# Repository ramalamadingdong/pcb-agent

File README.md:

# pcb-agent

Design a circuit board end to end with an agent. Parts, netlist, placement,
routing, gerbers a fab will build. You review, it does the work.

<p align="center"><em>The example board —
<a href="examples/unoq-power-shield">examples/unoq-power-shield</a>, 49 components
on four layers, routed to 0 unconnected and 0 clearance violations. A KiCad render
of the design files in this repo; <strong>no physical board has been
fabricated</strong>.</em></p>

The method: **the design lives in a CSV, not in KiCad.** One row per pin.
Scripts build the schematic and the board from it. Nothing in the KiCad files
is edited by hand — to change the circuit you edit a row and rebuild. Then
five levels of checking, the last of which parses the exported gerbers,
because the gerbers are what the factory builds.

Written up in full at
[mouro.ai/blog/pcb-design-with-ai](https://mouro.ai/blog/pcb-design-with-ai/)
— why the CSV is the source of truth, the tool behaviour each pass exists
to survive, and what the example board cost to finish.

**New here? [docs/end-to-end.md](docs/end-to-end.md)** is the whole path in
one page: install, prove the toolchain on the example, then your own board
from an idea to a fab package.

## Status: passes landed, example board unproven

The build passes are in `scripts/build/` and the whole pipeline runs end to
end against the example board: netlist → schematic (clean round-trip diff) →
board → netclasses → floorplan → holes → zones/fanout → freerouting →
completion → fab export → checker. As of 2026-08-30 the example has passed
its pre-order gates — **0 unconnected, 0 clearance violations** across 5
identical DRC runs, `validate_gerbers` 14/0, `check_placement` 5/0, ERC
clean, every residual DRC item explained in its `rev-1-plan.md` ledger — but
**no physical board has been fabricated yet**. Until one comes back and powers on, treat
`examples/unoq-power-shield` as a pipeline exercise, not a verified
reference design.

**2026-09-30: three defects found and fixed, example rebuilt.** New gates
caught three real defects that the earlier gates had passed:

- **J4 (Qwiic) was rotated 180°.** Its socket opened into the board.
  `check_placement` now derives which way a connector faces from its
  rotation. J4 is at 0° now.
- **16 pads on eight rotated passives lay along the part axis.**
  `fix_pad_angles --check` now gates on it.
- **`finish_routes` laid redundant copper on already-routed nets.** Its
  connectivity model never joined a segment's two ends. That is fixed, and
  roughly 200 redundant segments and 69 vias are gone.

The example was rebuilt from `netlist.csv` in the pinned container.
`make check` passes every gate:

- ERC: 0 errors.
- Pad angles: all correct.
- DRC ×5: 13 errors, all in the `[[drc.accept]]` ledger with reasons, 0
  unconnected, identical in every run.
- `check_placement`: 11/0.
- `validate_gerbers`: 15/0, including the IPC-D-356 netlist against
  `netlist.csv`, 159/159 pins.

It is still **unfabricated**. See `rev-1-plan.md` for what remains at order
time.

If you want only the fab-output checker, it stands alone with no dependencies
at [gerber-check](https://github.com/ramalamadingdong/gerber-check).

Platform honesty: developed and verified on Linux (WSL) — the container
path, the clean-box doctor advice, and the whole pipeline. **macOS is
untested**: `doctor.py`'s KiCad.app python path was written from
documentation, not a Mac, and is the most likely thing to be wrong. If you
hit it, an issue with your `doctor.py` output is gold.

## Setup

```bash
git clone https://github.com/ramalamadingdong/pcb-agent && cd pcb-agent
python3 scripts/doctor.py
```

The doctor names every missing piece and the fix for your OS. Five things have
to line up — KiCad (9 or 10, **matching the major your boards use**: a KiCad 9
pcbnew returns None loading a KiCad 10 board, no error), KiCad's bundled
Python, a JVM matching your Freerouting, the Freerouting jar, and `uv` — and
each fails in a way that wastes an afternoon if you don't know what you're
looking at.

### Or: the container

The headless stages run in a container instead, so KiCad, Java and
Freerouting never need installing by hand:

```bash
make setup     # builds the pcb-agent image; fetches the pinned Freerouting
               # jar to tools/ for native runs, checksum-verified
make doctor    # reports what the container satisfies
make build route export check   # run in-container automatically when the
                                # image exists (BOARD_DIR picks the board)
```

`./run.sh <cmd>` runs any command in the container with the repo mounted at
/work, as your uid/gid. You still install KiCad natively to *look* at the
board — the container has no GUI (the one X11 artifact inside is xvfb, a
virtual framebuffer that exists solely because Freerouting 1.9.0 asks for a
screen size it never uses). The base image is digest-pinned (`KICAD_BASE` in
the Makefile) and must match your native KiCad major; the doctor warns on
drift. kicad/kicad images are linux/amd64 — Apple Silicon runs them under
emulation.

Then, in Claude Code:

```
/plugin marketplace add aklofas/kicad-happy
/plugin install kicad-happy@kicad-happy
```

Eleven KiCad skills by Andrew Klofas — datasheet extraction, EMC, SPICE,
sourcing from DigiKey, Mouser, LCSC and element14, fab prep for JLCPCB and
PCBWay. MIT. This is the install that matters most.

## Use

```
/new-board     an idea, interviewed into a cited plan and a netlist.csv
/build         netlist.csv -> schematic -> board -> placement -> zones -> silk
/route         snapshot -> Freerouting -> DRC x5 -> gerbers
/check         ERC, pad angles, DRC x5, placement, and the fab package, all gated
/improve-placement   look at where routing got stuck, try floorplan edits,
               keep only what a rebuild + re-route measures as better
/doctor        is this machine able to run any of it
```

`/new-board` stops twice for your sign-off: once after the interview, once
before it writes the netlist. Those stops are the safety story. An
idea-to-board prompt with no stops will produce sixty confident rows of
hallucinated pin numbers and you won't find out until the boards arrive.

The whole path, install to fab package:
[docs/end-to-end.md](docs/end-to-end.md). From netlist to fab package for
your own design, in more detail:
[docs/your-own-board.md](docs/your-own-board.md) — the board.toml sections,
the placement loop, and the traps this repo already paid for.

## What's here and what isn't

Working now:

- **`scripts/validate_gerbers.py`** — the level-4 checker. Reads exported
  gerbers and drill files as text. No dependencies, no install, doesn't need
  KiCad. Runs on any fab package from any tool. See below.
- **`scripts/build/check_placement.py`** — the board-level checker, and the
  other half of `make check`. Two things the gerber checker structurally
  cannot see: whether every `[[connectors]]` part can actually be **plugged
  into** (mating face reaches the outline, corridor for plug and cable clear —
  mounting holes inflated to the *screw head*, which is the thing actually in
  the way and which no courtyard in the file describes), and copper in a
  keepout named by object (`R12 pad 2`, `via GND at 41.20,18.05`) instead of
  by aperture. Runs in about a second off the board file, so a floorplan
  mistake surfaces while the floorplan is still what you are editing, not
  fifteen minutes later in the fab package.
- **`scripts/build/drc_sample.py`, `erc_check.py`**: levels 1 and 2 as
  gates, not reports. DRC runs 5×, and anything unexplained in any run fails.
  The explanations live in `board.toml` as `[[drc.accept]]` entries, each
  with its reason. An entry that stops matching fails too. Connectivity
  parity (the board's nets against the schematic) is gated even though KiCad
  ships it as a warning.
- **`check_netlist`** in `validate_gerbers.py`: level 0 on what ships. The
  export includes an IPC-D-356 netlist (the file a fab's electrical test
  probes against), and the checker holds it to `netlist.csv` pin by pin.
- **`scripts/build/render_review.py`** (`make render`): a PNG per copper layer
  with the ratsnest in red and completion-pass copper in orange, for level 3
  and `/improve-placement`. **`score_route.py`** (`make score`): one
  comparable score for a routed board, measured, never read from the
  router's log.
- **`scripts/doctor.py`**: environment preflight.
- **`CLAUDE.md`** — the rules. This is what keeps an agent from undoing the
  work: don't edit board files, fixes go in the pipeline, every pass
  idempotent, don't trust a tool's self-report, get the document.
- **`commands/`**: the six slash commands.
- **`templates/`** — `netlist.csv` schema and a commented `board.toml`.

Also here now:

- **`scripts/build/`** — the build passes, ported from the pipeline that
  shipped real boards. They encode specific tool behaviour discovered by
  getting boards back broken — `repair_pads` restoring rotation as well as
  position, the net-table assertion after every board write, the
  four-spacing fanout check, `silk_finish` repositioning every refdes —
  with the comments explaining why each guard exists.

Not here yet:

- **An example board that has been powered on.** `examples/unoq-power-shield`
  has a cited plan and netlist, but until one is built and brought up it is a
  reference design nobody has verified.

## The gerber checker on its own

Useful even if you never adopt the rest:

```bash
python3 scripts/validate_gerbers.py --init      # writes board.toml
python3 scripts/validate_gerbers.py ./fab/
```

Catches what passes ERC, passes DRC, passes every fab export, and still ships
a broken board:

| Check | Why nothing else sees it |
| --- | --- |
| Signal traces on a layer you declared a plane | DRC doesn't know it's a plane. Breaks the reference for anything routed over it. |
| Power nets at default trace width | Generated netclass patterns (`VCC*`, `VDD*`, `+*V`) match none of the usual net names. Nothing errors, the traces just come out thin. |
| Missing mounting holes | Not netlist objects. Nothing emits them unless you write the pass. |
| Silkscreen past the board outline | The fab clips it. Boards print bare. |
| Fiducials missing, collinear, or in a keepout | Keepout rules ban pours, tracks and vias — not pads. |
| Too few thermal vias under an exposed pad | No rule covers "enough". |
| RF trace over budget | Nothing measures it. |

Rules you don't configure report `SKIP`, not `PASS`. A check you haven't
written isn't a check that passed.

Export with X2 attributes on — net names and fiducial tags ride in those, and
without them the net-aware checks go blind.

## Scope

This gets you to a package a fab will build and a written reason behind every
choice in it. Respins in hours instead of days, because the fixes are in code.

It doesn't replace bring-up. Done and clean and fabricated isn't the same as
working.

## Credit

- [kicad-happy](https://github.com/aklofas/kicad-happy) — Andrew Klofas, MIT
- [kicad-tools](https://github.com/rjwalters/kicad-tools) — RJ Walters, MIT
- [Freerouting](https://github.com/freerouting/freerouting)
- [KiCad-AI-Assistant](https://github.com/paul356/KiCad-AI-Assistant) (MIT,
  © 2025 Lama Al Rajih): `render_review.py`'s per-layer panels and MST
  ratsnest follow the approach of its board renderer. The ideas are
  borrowed; no code was copied.
- [KiCad](https://www.kicad.org/)

GPL-3.0 — the build passes import `pcbnew`, which is GPL-3.0, and now that
they've landed the repo follows.
[gerber-check](https://github.com/ramalamadingdong/gerber-check) is pure
stdlib text parsing, links nothing, and stays MIT.

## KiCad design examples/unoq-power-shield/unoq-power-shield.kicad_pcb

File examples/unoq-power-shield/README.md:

# UNO Q power & I/O demo shield

<table>
<tr>
<td width="50%"></td>
<td width="50%"></td>
</tr>
<tr>
<td align="center"><em><strong>Populated</strong> — every footprint with its 3D
model. The four edge strips and J5 are drawn as plain male pin headers because
that is what the footprint's model is; the real parts are <strong>stacking</strong>
headers — female sockets on top, long tails passing down into the UNO Q — and
they ship <strong>DNP</strong> (see below), so an assembled board arrives with
those pads bare.</em></td>
<td align="center"><em><strong>Bare</strong> — the PCB the fab builds from the
gerbers: four-layer copper, mask, silk, and the three X2-tagged fiducials the
assembler's vision system needs.</em></td>
</tr>
</table>

**Status: UNBUILT.** No physical board of this design has been fabricated
or powered on yet. Until one has, treat this as a reference for exercising
the pipeline, not a verified design.

The *design* has passed its pre-order gates (2026-08-30): routed with
**0 unconnected** and **0 clearance violations** across 5 identical DRC
runs, `validate_gerbers` 14/0, ERC clean, every BOM line in stock. The 17
residual DRC items are all form-factor or courtyard-graze artifacts,
individually explained in the ledger in [rev-1-plan.md](rev-1-plan.md).
Passing gates is not the same as working hardware — the UNBUILT warning
above stands until a board has been powered on.

**The stacking headers ship DNP** — the assembled board cannot plug into
anything until you solder a stacking header set into the four plated hole
strips. Any classic Arduino R3 stacking kit fits: SparkFun PRT-11417 or
Adafruit #85, about **$2**. This is deliberate: assembly houses don't stock
stacking headers, and a flush-soldered normal header would make the shield
unstackable.

The example board for this repo — the design a first-time user builds
**before trusting the pipeline with their own board**. If this builds,
routes, checks, and comes back from the fab working, the pipeline works.
That is all it proves: it says nothing about whether any *other* design is
right, and it is not a product.

## What it is

A shield for the [Arduino UNO Q](https://docs.arduino.cc/hardware/uno-q)
(classic UNO outline, stacking headers):

- **Screw-terminal VIN, 7–24 V** — the UNO Q's own DC input range. Feeds
  the Q's VIN pin and a local TPS54331 buck making 5 V for shield loads,
  behind reverse-polarity protection (the terminal a first-timer wires
  backwards).
- **INA226 high-side monitor** on the VIN rail, upstream of everything, so
  the stack reports its **own total consumption** over I²C (address 0x40,
  on D20/D21; ALERT on ~D3).
- **Four bidirectional level-shift channels** (BSS138 + 10 k) between the
  headers and 5 V peripherals, on D2/D4/D7/D8. **The UNO Q's headers are
  3.3 V logic, not the classic UNO's 5 V** — wiring 5 V gear straight in is
  the most common way this board gets damaged, and this circuit is the fix.
  **Signalling limit: ~300 kHz.** The 10 k pull-ups against ~30 pF of load
  give ~0.3 µs rise times: fine for GPIO, buttons, slow UART, and 100 kHz
  I²C-style traffic; **not for SPI above ~300 kHz and not for NeoPixels**
  (WS2812 timing needs edges these channels cannot produce). That is a
  documented property of the classic BSS138 shifter, not a defect.
- **Qwiic passthrough** (2× JST-SH, daisy-chain) on the same I²C bus.
- **RGB status LED** on ~D9/~D10/~D11, active-low, for sketches to drive.

Design record: [rev-1-plan.md](rev-1-plan.md) — every requirement cited to
Arduino's own documents, every part checked against the JLCPCB library,
every number with its arithmetic shown. Rules: [board.toml](board.toml).

## What it teaches

Each `board.toml` rule exists here for a visible physical reason:

| Rule | Why it's real on this board |
| --- | --- |
| thermal vias | the buck's exposed pad is its only real heatsink |
| power trace width | VIN carries up to 4 A; IPC-2221 sets the number |
| mounting holes | all four fixed by the UNO pattern — extracted from Arduino's own drill file |
| planes | solid ground under a switching converter |
| keepout | the UNO Q's Wi-Fi antenna is directly under the board's top-left corner — copper there detunes it |
| fiducials, X2-tagged | assembly needs them, and untagged ones are invisible to gerber-level checking |

## What it costs (estimate, 2026-08)

- 4-layer PCB, 5 pcs: ~$8–15
- JLCPCB SMT assembly (2–5 boards): setup ~$25, ~10 Extended-part feeder
  fees ~$30, parts ~$2.5/board, THT screw terminals hand-solder fee
- **Ballpark: $70–90 for a small assembled batch**
- Stacking headers are DNP — fit any Arduino stacking-header kit (~$2)

## Power behavior

| Supply | Result |
| --- | --- |
| USB-C only | UNO Q runs; shield 5 V rail is off (needs VIN) — by design |
| VIN only | everything runs; the Q is powered through its VIN pin |
| both | fine — the Q diode-ORs internally; the shield never drives the 5 V or 3V3 header pins |

## Attribution

The UNO Q facts in this design — pinout, electrical limits, mechanical
coordinates, antenna location — come from Arduino's official documents and
CAD files for the UNO Q (ABX00162), © Arduino SA, licensed
[CC BY-SA 4.0](https://creativecommons.org/licenses/by-sa/4.0/):
datasheet, full pinout, schematics, and fab data, copies in
[docs/datasheets/](../../docs/datasheets/). The antenna keepout and
hole/header coordinates were extracted from the gerber and NC-drill files
Arduino publishes there. This example's own design files are MIT like the
rest of the repo; the CC BY-SA attribution above covers what was derived
from Arduino's documents.

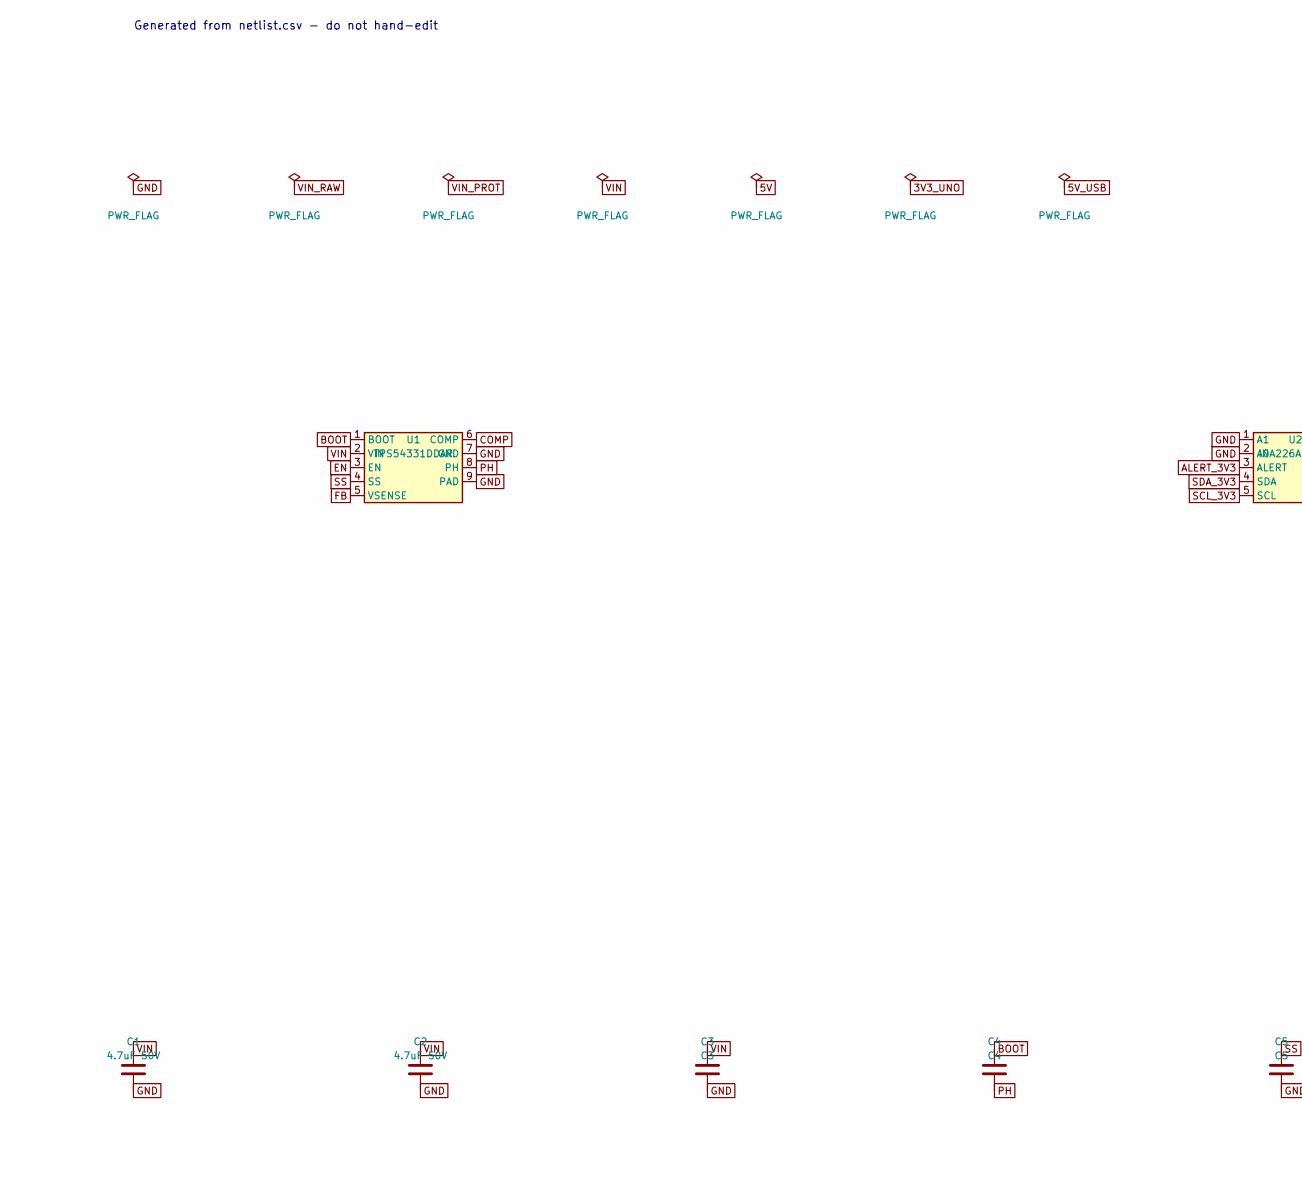
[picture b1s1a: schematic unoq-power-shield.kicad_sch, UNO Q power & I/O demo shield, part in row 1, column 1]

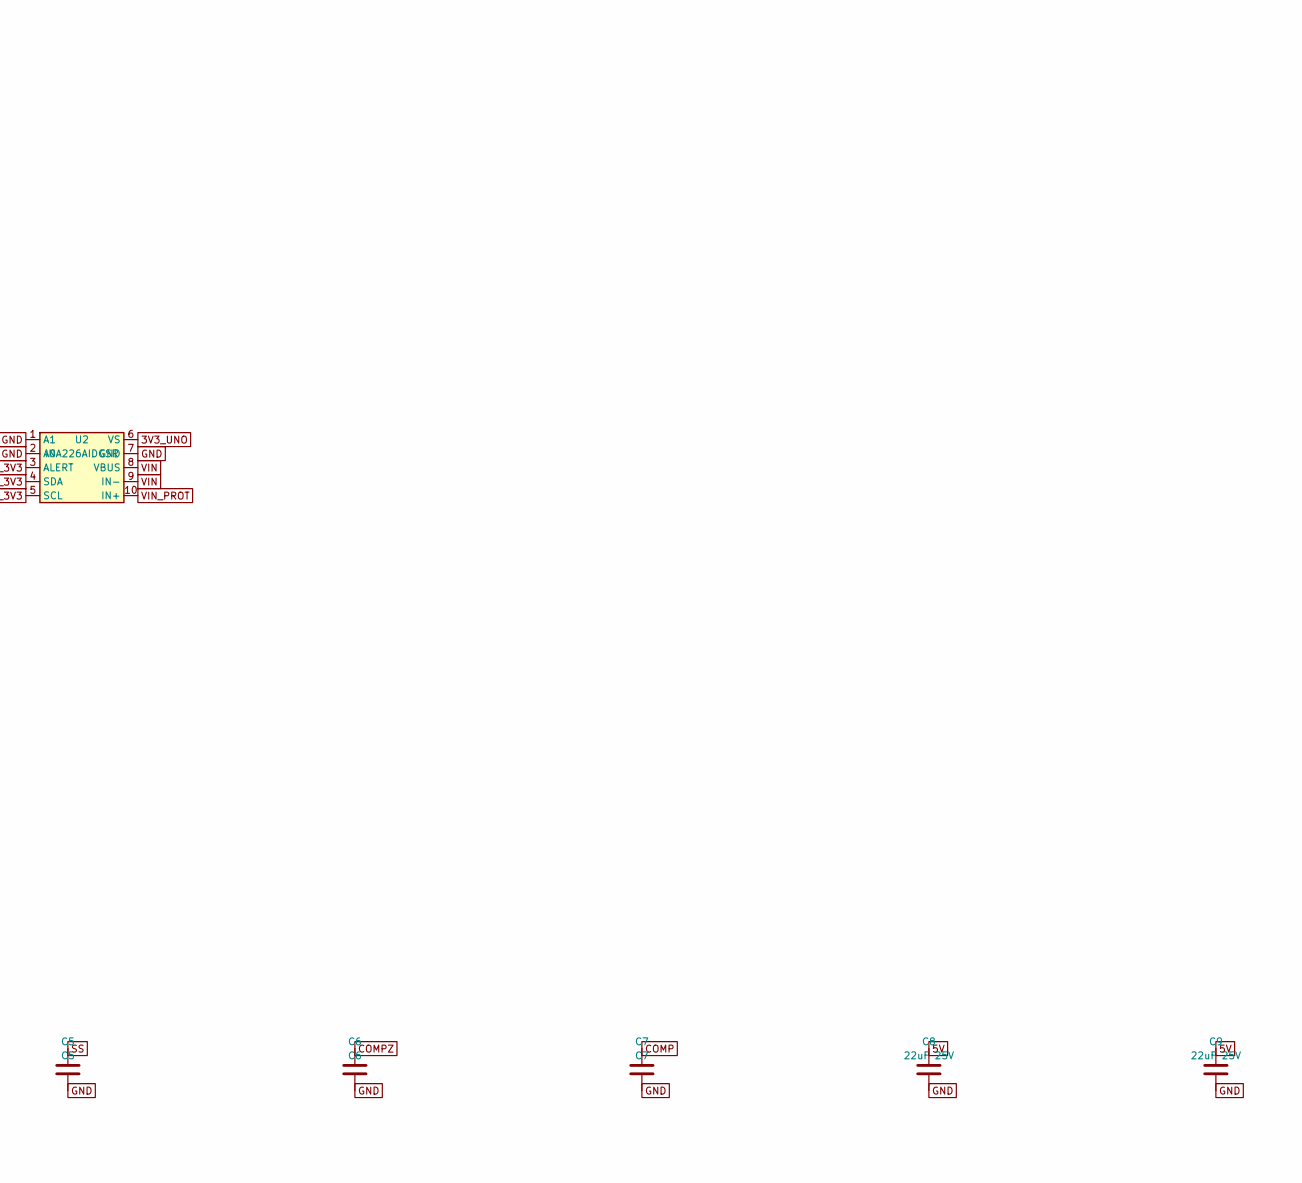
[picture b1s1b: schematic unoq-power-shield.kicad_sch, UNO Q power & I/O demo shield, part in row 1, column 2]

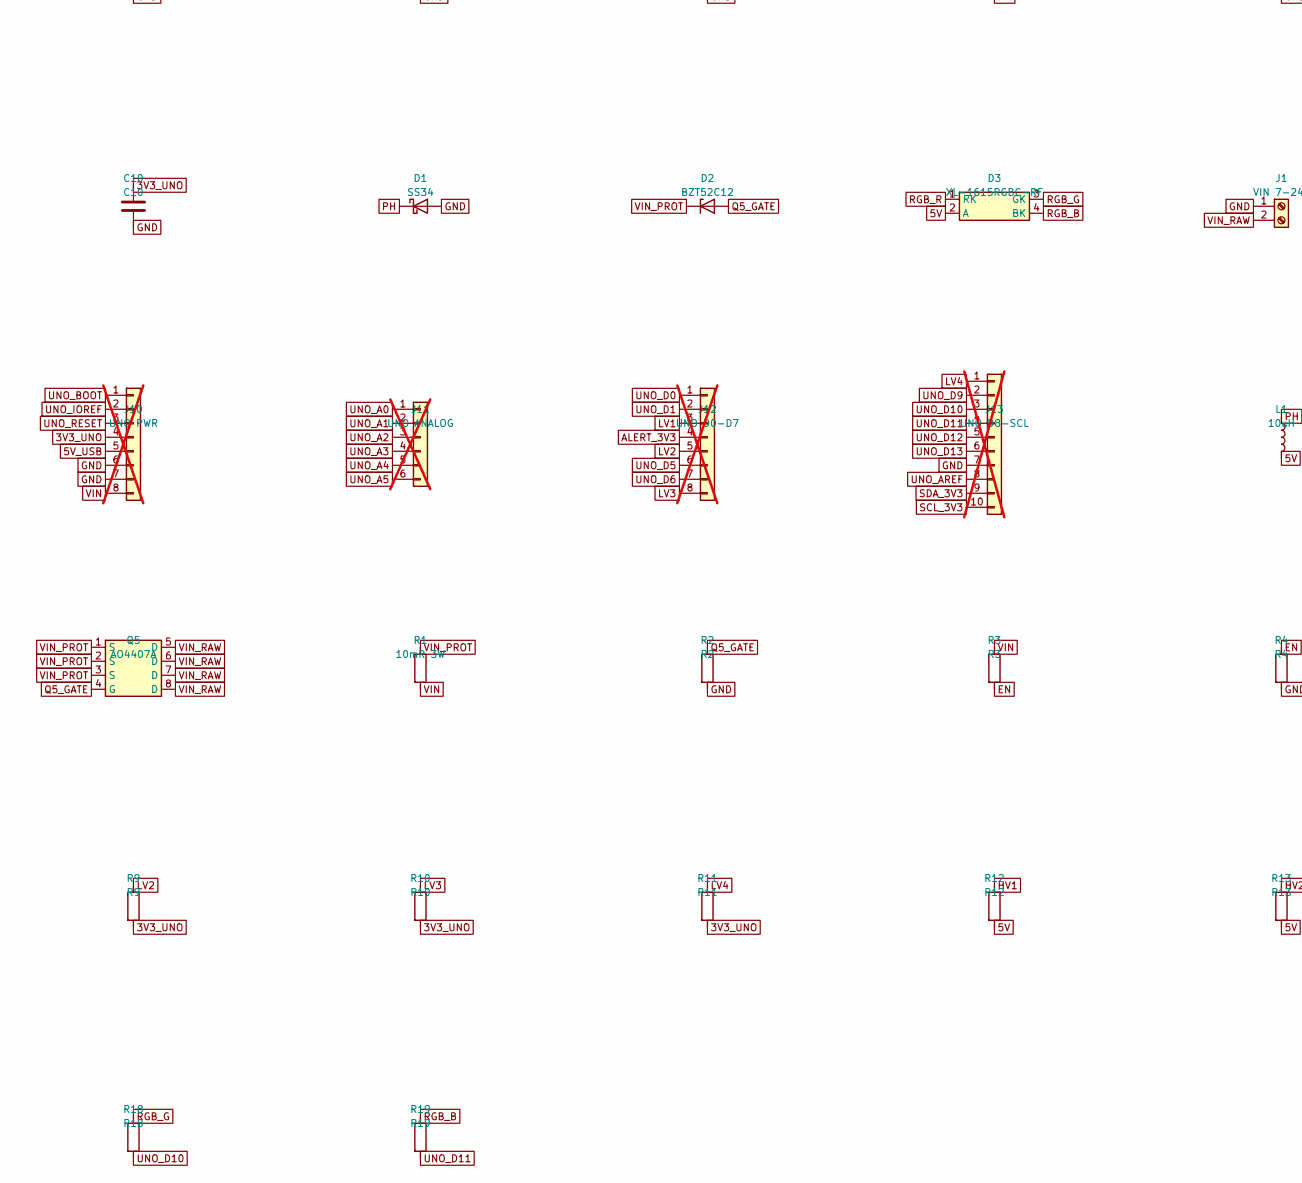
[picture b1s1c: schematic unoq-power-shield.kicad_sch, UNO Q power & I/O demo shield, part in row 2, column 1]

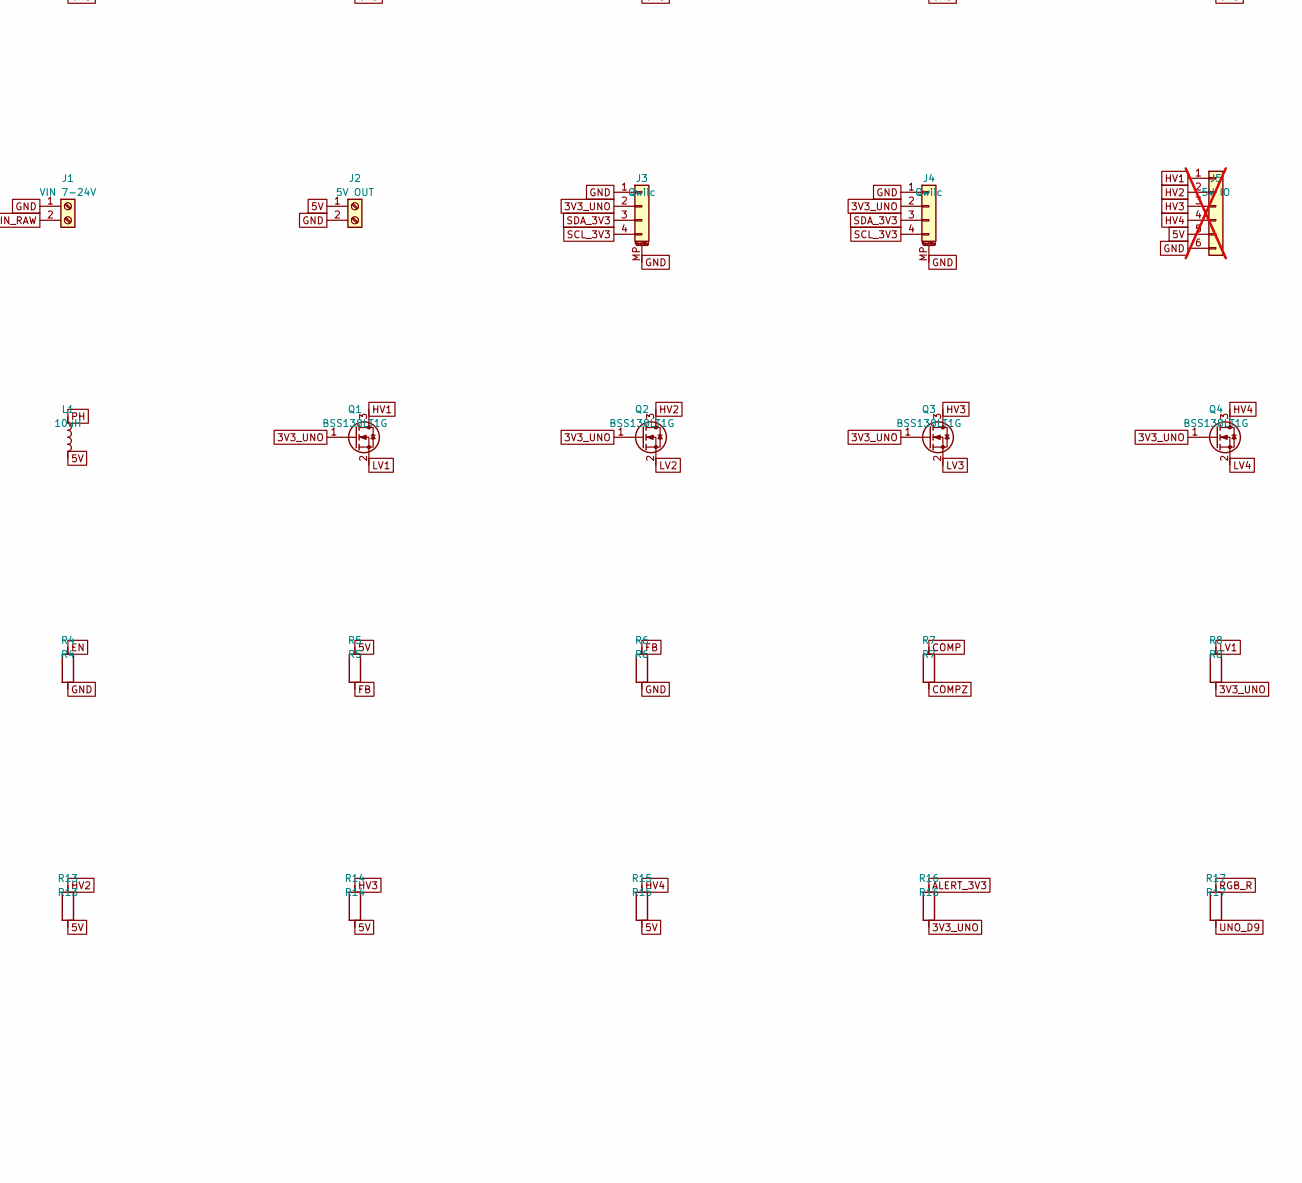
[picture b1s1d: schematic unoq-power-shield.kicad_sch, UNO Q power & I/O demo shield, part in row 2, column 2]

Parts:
C1, C2: 4.7uF 50V; C_1206_3216Metric
C3: C3; C_0603_1608Metric
C4: C4; C_0603_1608Metric
C5: C5; C_0603_1608Metric
C6: C6; C_0603_1608Metric
C7: C7; C_0603_1608Metric
C8, C9: 22uF 25V; C_1206_3216Metric
C10: C10; C_0603_1608Metric
D1: SS34; D_SMA
D2: BZT52C12; D_SOD-123
D3: XL-1615RGBC-RF; XL1615RGBC
J1: VIN 7-24V; KF301_5.0_2P
J2: 5V OUT; KF301_5.0_2P
J3, J4: Qwiic; JST_SH_SM04B-SRSS-TB_1x04-1MP_P1.00mm_Horizontal
J5: 5V IO; PinHeader_1x06_P2.54mm_Vertical; not fitted
J10: UNO PWR; PinHeader_1x08_P2.54mm_Vertical; not fitted
J11: UNO ANALOG; PinHeader_1x06_P2.54mm_Vertical; not fitted
J12: UNO D0-D7; PinHeader_1x08_P2.54mm_Vertical; not fitted
J13: UNO D8-SCL; PinHeader_1x10_P2.54mm_Vertical; not fitted
L1: 10uH; SWPA6045S
Q1, Q2, Q3, Q4: BSS138LT1G; SOT-23
Q5: AO4407A; SOIC-8_3.9x4.9mm_P1.27mm
R1: 10mR 3W; R_2512_6332Metric
R2: R2; R_0603_1608Metric
R3: R3; R_0603_1608Metric
R4: R4; R_0603_1608Metric
R5: R5; R_0603_1608Metric
R6: R6; R_0603_1608Metric
R7: R7; R_0603_1608Metric
R8: R8; R_0603_1608Metric
R9: R9; R_0603_1608Metric
R10: R10; R_0603_1608Metric
R11: R11; R_0603_1608Metric
R12: R12; R_0603_1608Metric
R13: R13; R_0603_1608Metric
R14: R14; R_0603_1608Metric
R15: R15; R_0603_1608Metric
R16: R16; R_0603_1608Metric
R17: R17; R_0603_1608Metric
R18: R18; R_0603_1608Metric
R19: R19; R_0603_1608Metric
U1: TPS54331DDAR; TI_SO-PowerPAD-8
U2: INA226AIDGSR; MSOP-10_3x3mm_P0.5mm

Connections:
ALERT_3V3: J12.4, R16.1, U2.3 (ALERT)
BOOT: C4.1, U1.1 (BOOT)
COMP: C7.1, R7.1, U1.6 (COMP)
COMPZ: C6.1, R7.2
EN: R3.2, R4.1, U1.3 (EN)
FB: R5.2, R6.1, U1.5 (VSENSE)
HV1: J5.1, Q1.3 (D), R12.1
HV2: J5.2, Q2.3 (D), R13.1
HV3: J5.3, Q3.3 (D), R14.1
HV4: J5.4, Q4.3 (D), R15.1
LV1: J12.3, Q1.2 (S), R8.1
LV2: J12.5, Q2.2 (S), R9.1
LV3: J12.8, Q3.2 (S), R10.1
LV4: J13.1, Q4.2 (S), R11.1
PH: C4.2, D1.1 (K), L1.1, U1.8 (PH)
Q5_GATE: D2.2 (A), Q5.4 (G), R2.1
RGB_B: D3.4 (BK), R19.1
RGB_G: D3.3 (GK), R18.1
RGB_R: D3.1 (RK), R17.1
SCL_3V3: J3.4, J4.4, J13.10, U2.5 (SCL)
SDA_3V3: J3.3, J4.3, J13.9, U2.4 (SDA)
SS: C5.1, U1.4 (SS)
UNO_A0: J11.1
UNO_A1: J11.2
UNO_A2: J11.3
UNO_A3: J11.4
UNO_A4: J11.5
UNO_A5: J11.6
UNO_AREF: J13.8
UNO_BOOT: J10.1
UNO_D0: J12.1
UNO_D1: J12.2
UNO_D5: J12.6
UNO_D6: J12.7
UNO_D9: J13.2, R17.2
UNO_D10: J13.3, R18.2
UNO_D11: J13.4, R19.2
UNO_D12: J13.5
UNO_D13: J13.6
UNO_IOREF: J10.2
UNO_RESET: J10.3

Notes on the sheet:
Generated from netlist.csv - do not hand-edit

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
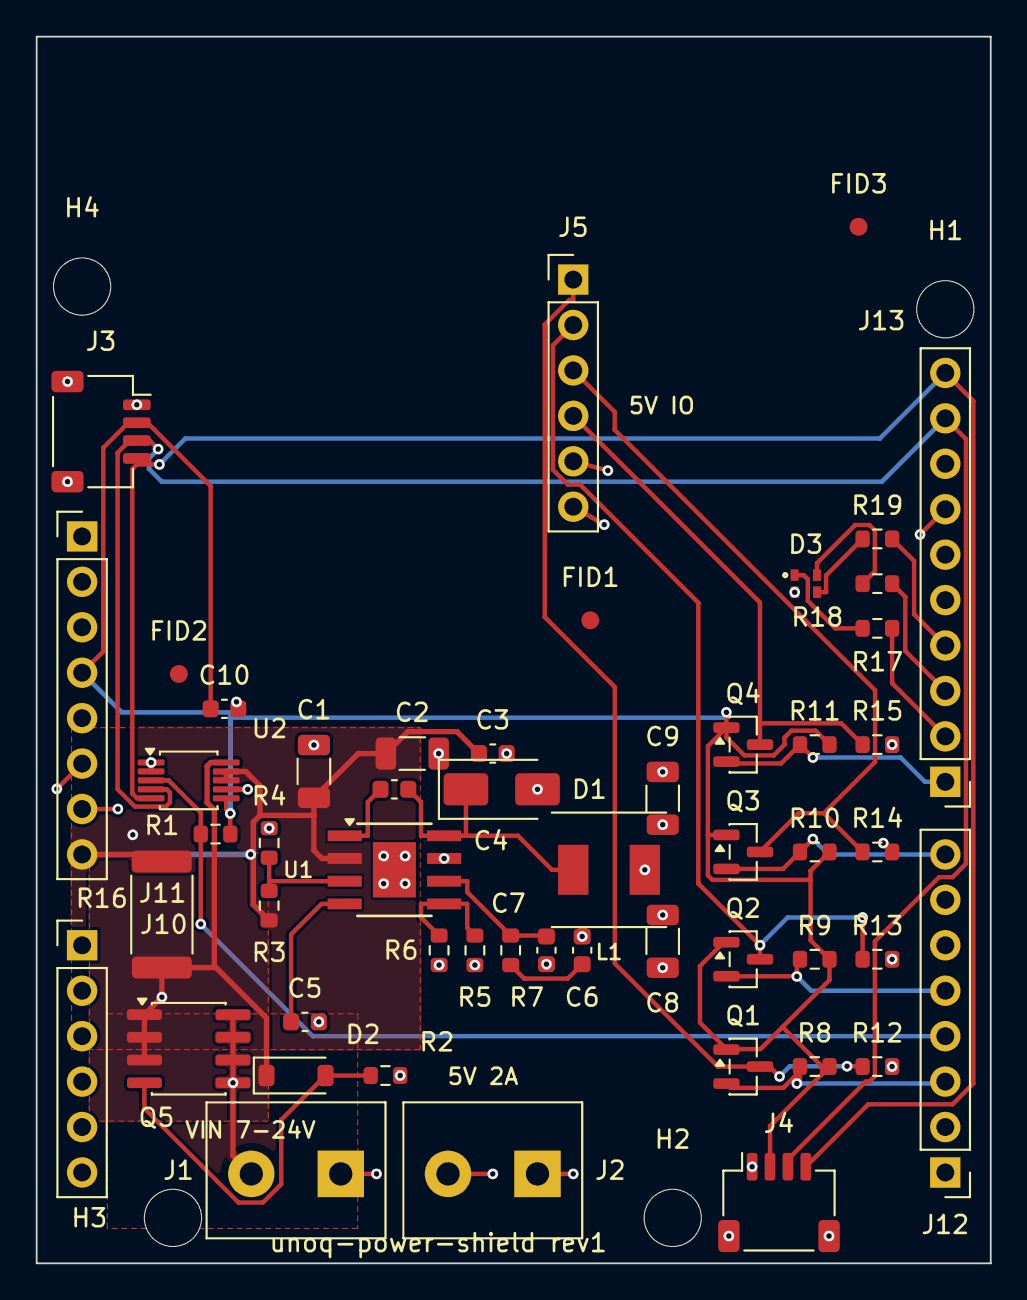
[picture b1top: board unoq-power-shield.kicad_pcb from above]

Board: 4 copper layers, 53.3 x 68.6 mm, 56 parts (0 on the bottom side), 31 nets.

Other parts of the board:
FID1, FID2, FID3: Fiducial_pcb-agent
H1, H2, H3, H4: MountingHole_3.2mm
